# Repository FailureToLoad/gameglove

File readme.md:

# Game Glove

Having grown tired of trying different keyboard layouts that all always felt slightly off, I set out to design a gaming peripheral that felt right.

## Objectives

### 1. Small footprint

This is a perpipheral that will sit along side my normal keyboard so it should be half the size of a 60% at most.

### 2. Should be able to press the 2 and 3 keys with middle finger

I can't shake this very specific muscle memory, so may as well design around it.

### 3. Row aligned, column staggered, WASD oriented

I've never been able to hit keys like Z, X, and C reliably. My brain refuses to memorize the meat signals to reach down, then laterally. That led me to at least remove the lateral movement by going for something ortholinear-ish.

Pure ortholinear was uncomfortable for me, but column staggered ortho made a lot of sense. The problem is that most column staggered layouts base the spacing off of home-row hand positioning. This is for gaming, so the spacing should be oriented around WASD positioning.

### 4. Modifier keys must be larger than 1u

From trying pure ortholinear, my hands felt fairly cramped with 1u modifier keys.

## V1

After a fair amount of iteration and prototyping, I've landed on the following.

### 4x5 + 4 Layout

I liked the look of 6 keys on row 1 and row 5 felt just right at 3 keys.

### Row staggered first and last row

Row staggering the first row got me my 2/3 key situation I wanted. The last row was positioned based off of where my thumb comfortably sits.

I cannot stress how much time I spent measuring the thumb positioning. It is maddening how many ways there are to do it wrong.

### WASD oriented

I shifted the spacing so that W defines the "peak" of the column staggering.

### Modifier key sizing

I changed the shift to be 1.75u to avoid non-standard sizing issues with keycap sets and then right-justified the modifiers to conform to the row-aligned, column-staggered requirement.

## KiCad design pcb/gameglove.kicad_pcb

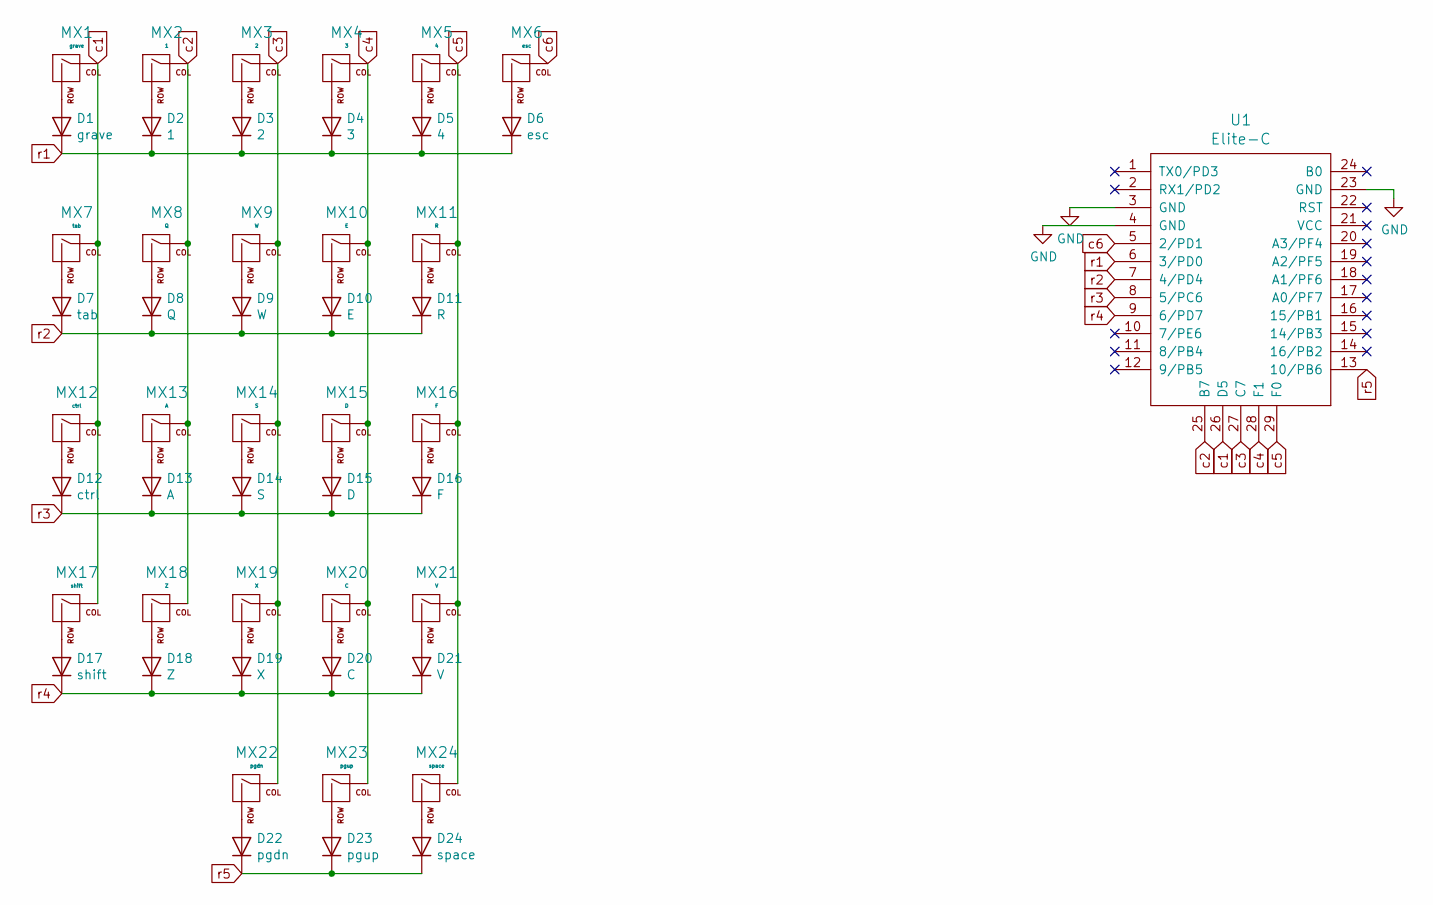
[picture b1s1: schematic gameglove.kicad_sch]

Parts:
D1: grave; D_axial
D2: 1; D_axial
D3: 2; D_axial
D4: 3; D_axial
D5: 4; D_axial
D6: esc; D_axial
D7: tab; D_axial
D8: Q; D_axial
D9: W; D_axial
D10: E; D_axial
D11: R; D_axial
D12: ctrl; D_axial
D13: A; D_axial
D14: S; D_axial
D15: D; D_axial
D16: F; D_axial
D17: shift; D_axial
D18: Z; D_axial
D19: X; D_axial
D20: C; D_axial
D21: V; D_axial
D22: pgdn; D_axial
D23: pgup; D_axial
D24: space; D_axial
MX1: grave; MXOnly-1U-NoLED
MX2: 1; MXOnly-1U-NoLED
MX3: 2; MXOnly-1U-NoLED
MX4: 3; MXOnly-1U-NoLED
MX5: 4; MXOnly-1U-NoLED
MX6: esc; MXOnly-1U-NoLED
MX7: tab; MXOnly-1.5U-NoLED
MX8: Q; MXOnly-1U-NoLED
MX9: W; MXOnly-1U-NoLED
MX10: E; MXOnly-1U-NoLED
MX11: R; MXOnly-1U-NoLED
MX12: ctrl; MXOnly-1.75U-NoLED
MX13: A; MXOnly-1U-NoLED
MX14: S; MXOnly-1U-NoLED
MX15: D; MXOnly-1U-NoLED
MX16: F; MXOnly-1U-NoLED
MX17: shift; MXOnly-1.75U-NoLED
MX18: Z; MXOnly-1U-NoLED
MX19: X; MXOnly-1U-NoLED
MX20: C; MXOnly-1U-NoLED
MX21: V; MXOnly-1U-NoLED
MX22: pgdn; MXOnly-1U-NoLED
MX23: pgup; MXOnly-1U-NoLED
MX24: space; MXOnly-2U-NoLED
U1: Elite-C; Elite-C-castellated-29pin-holes

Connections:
GND: U1.3 (GND), U1.4 (GND), U1.23 (GND)
unnamed: D1.2 (A), MX1.2 (ROW)
unnamed: D2.2 (A), MX2.2 (ROW)
unnamed: D3.2 (A), MX3.2 (ROW)
unnamed: D4.2 (A), MX4.2 (ROW)
unnamed: D5.2 (A), MX5.2 (ROW)
unnamed: D6.2 (A), MX6.2 (ROW)
unnamed: D7.2 (A), MX7.2 (ROW)
unnamed: D8.2 (A), MX8.2 (ROW)
unnamed: D9.2 (A), MX9.2 (ROW)
unnamed: D10.2 (A), MX10.2 (ROW)
unnamed: D11.2 (A), MX11.2 (ROW)
unnamed: D12.2 (A), MX12.2 (ROW)
unnamed: D13.2 (A), MX13.2 (ROW)
unnamed: D14.2 (A), MX14.2 (ROW)
unnamed: D15.2 (A), MX15.2 (ROW)
unnamed: D16.2 (A), MX16.2 (ROW)
unnamed: D17.2 (A), MX17.2 (ROW)
unnamed: D18.2 (A), MX18.2 (ROW)
unnamed: D19.2 (A), MX19.2 (ROW)
unnamed: D20.2 (A), MX20.2 (ROW)
unnamed: D21.2 (A), MX21.2 (ROW)
unnamed: D22.2 (A), MX22.2 (ROW)
unnamed: D23.2 (A), MX23.2 (ROW)
unnamed: D24.2 (A), MX24.2 (ROW)
c1: MX1.1 (COL), MX7.1 (COL), MX12.1 (COL), MX17.1 (COL), U1.26 (D5)
c2: MX2.1 (COL), MX8.1 (COL), MX13.1 (COL), MX18.1 (COL), U1.25 (B7)
c3: MX3.1 (COL), MX9.1 (COL), MX14.1 (COL), MX19.1 (COL), MX22.1 (COL), U1.27 (C7)
c4: MX4.1 (COL), MX10.1 (COL), MX15.1 (COL), MX20.1 (COL), MX23.1 (COL), U1.28 (F1)
c5: MX5.1 (COL), MX11.1 (COL), MX16.1 (COL), MX21.1 (COL), MX24.1 (COL), U1.29 (F0)
c6: MX6.1 (COL), U1.5 (2/PD1)
r1: D1.1 (K), D2.1 (K), D3.1 (K), D4.1 (K), D5.1 (K), D6.1 (K), U1.6 (3/PD0)
r2: D7.1 (K), D8.1 (K), D9.1 (K), D10.1 (K), D11.1 (K), U1.7 (4/PD4)
r3: D12.1 (K), D13.1 (K), D14.1 (K), D15.1 (K), D16.1 (K), U1.8 (5/PC6)
r4: D17.1 (K), D18.1 (K), D19.1 (K), D20.1 (K), D21.1 (K), U1.9 (6/PD7)
r5: D22.1 (K), D23.1 (K), D24.1 (K), U1.13 (10/PB6)

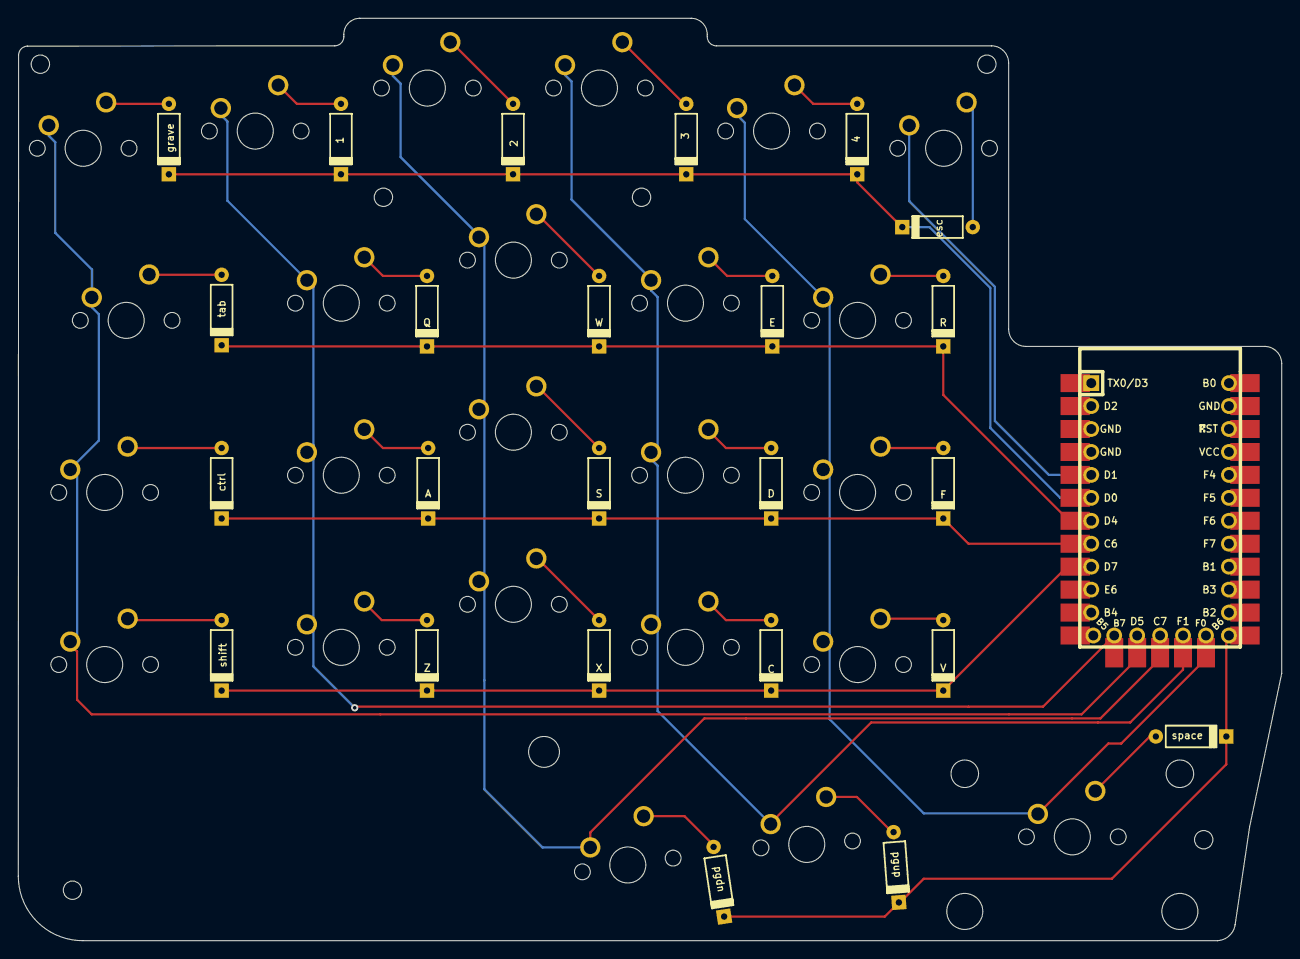
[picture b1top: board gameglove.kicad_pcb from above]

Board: 2 copper layers, 139.9 x 102.1 mm, 49 parts (0 on the bottom side), 36 nets.

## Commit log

2021-12-28 adds initial content
2021-12-28 adds layout image
2021-12-28 updates readme
2022-01-05 revises readme
